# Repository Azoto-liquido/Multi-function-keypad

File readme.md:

# Multi-function keypad

This is a 4 switches keypad with a rotary encoder and an OLED display, it has 2 LEDs and uses QMK Firmware.

I made it to learn a bit of this topic and I think it is perfect for general porpouse, everyday shortcuts and macros in gaming. Also in the little display you could write your name or a motd.

## Bill of Materials
- 4x Cherry MX Switches
- 4x DSA Keycaps
- 4x M3x16mm SHCS Bolts
- 2x sk6812mini LEDs
- 1x 0.91" 128x32 OLED Display
- 1x EC11 Rotary Encoder
- 1x XIAO RP2040
- 1x Case (2 printed parts)

## Cad
The 2 parts are held together with 4 M3x16mm SHCS Bolts without heatset inserts (the threads are cut directly into the plastic). The case has a 4 degrees titl for better ergonomics.

Made in Fusion 360.

## PCB

Schematic:

PCB:

## Firmware Overview
The firmware uses QMK Firmware and is fully configurable with VIA.
- The rotary encoder serves as a volume controller.
- The 4 keys can be assigned to any key with VIAA (https://caniusevia.com/).
- Holding down the 4th key will activate another layer in which the keys can be assigned to any other function.
- The OLED display can be assigned to display any text (Always in VIA).
- The 2 LEDs can display any color (This is also done in VIA).

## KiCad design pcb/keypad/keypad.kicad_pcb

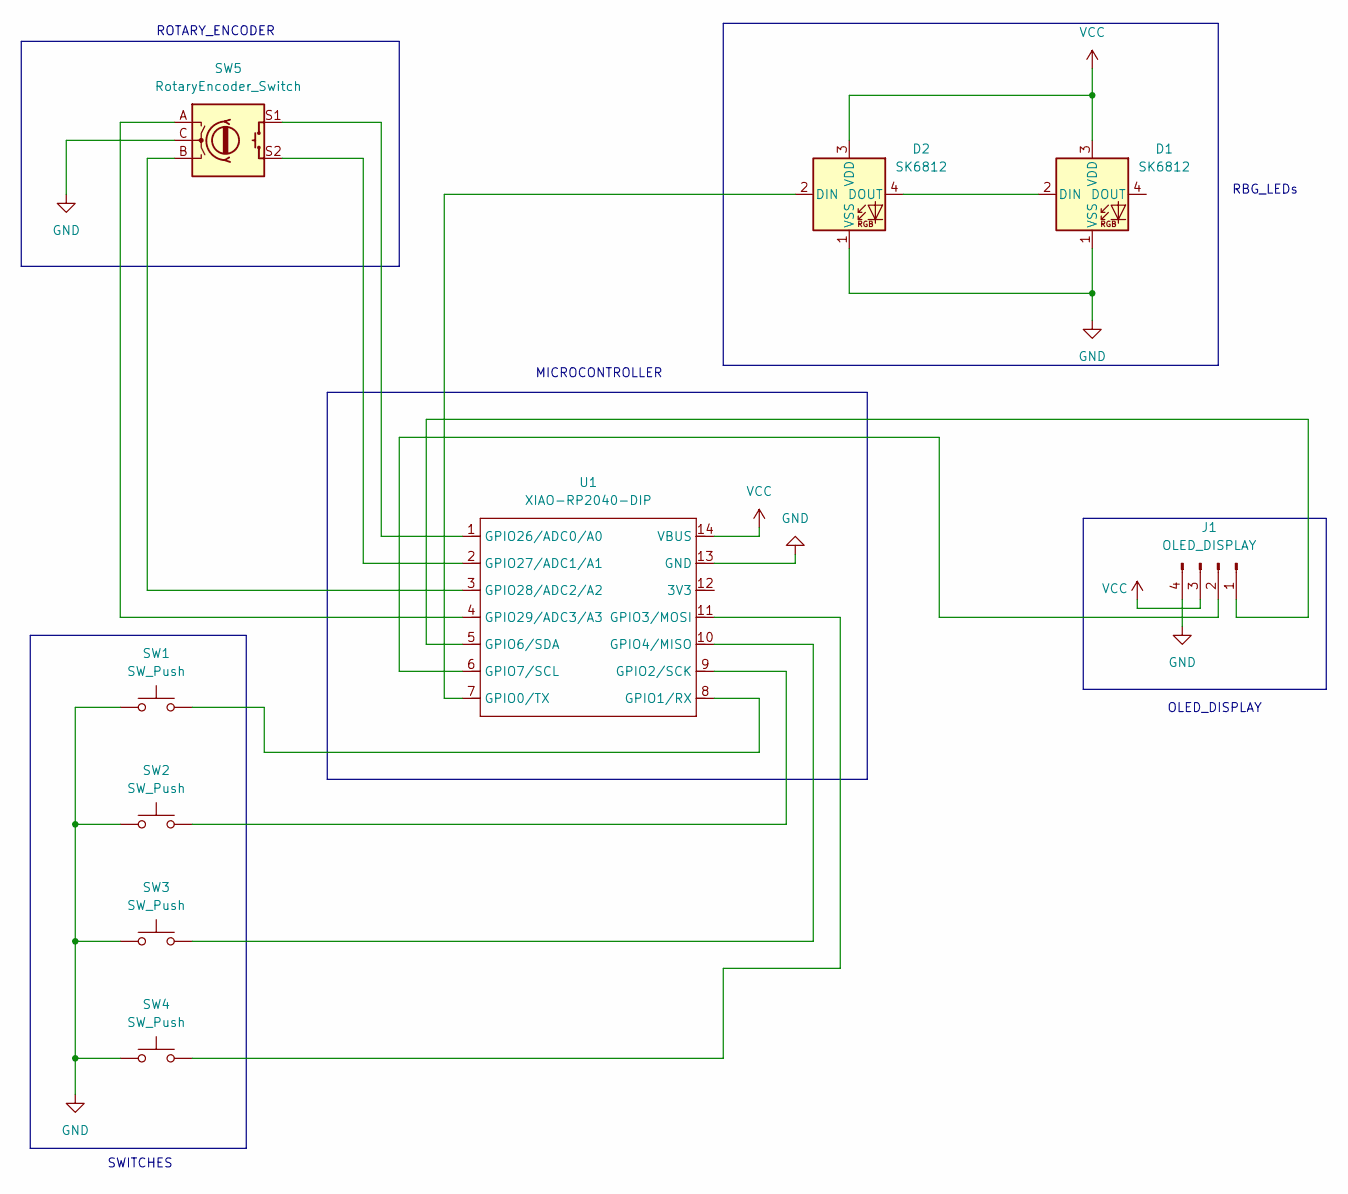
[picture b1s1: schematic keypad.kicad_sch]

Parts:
D1, D2: SK6812; LED_SK6812MINI_PLCC4_3.5x3.5mm_P1.75mm
J1: OLED_DISPLAY; PinHeader_1x04_P2.54mm_Vertical
SW1, SW2, SW3, SW4: SW_Push; SW_Cherry_MX_1.00u_PCB
SW5: RotaryEncoder_Switch; RotaryEncoder_Alps_EC11E-Switch_Vertical_H20mm
U1: XIAO-RP2040-DIP

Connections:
GND: D1.1 (VSS), D2.1 (VSS), J1.4, SW1.1, SW2.1, SW3.1, SW4.1, SW5.C, U1.13 (GND)
unnamed: D1.2 (DIN), D2.4 (DOUT)
unnamed: D2.2 (DIN), U1.7 (GPIO0/TX)
unnamed: J1.1, U1.5 (GPIO6/SDA)
unnamed: J1.2, U1.6 (GPIO7/SCL)
unnamed: SW1.2, U1.8 (GPIO1/RX)
unnamed: SW2.2, U1.9 (GPIO2/SCK)
unnamed: SW4.2, U1.11 (GPIO3/MOSI)
unnamed: SW3.2, U1.10 (GPIO4/MISO)
unnamed: SW5.S1, U1.1 (GPIO26/ADC0/A0)
unnamed: SW5.S2, U1.2 (GPIO27/ADC1/A1)
unnamed: SW5.B, U1.3 (GPIO28/ADC2/A2)
unnamed: SW5.A, U1.4 (GPIO29/ADC3/A3)
VCC: D1.3 (VDD), D2.3 (VDD), J1.3, U1.14 (VBUS)

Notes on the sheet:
OLED_DISPLAY
MICROCONTROLLER
RBG_LEDs
ROTARY_ENCODER
SWITCHES

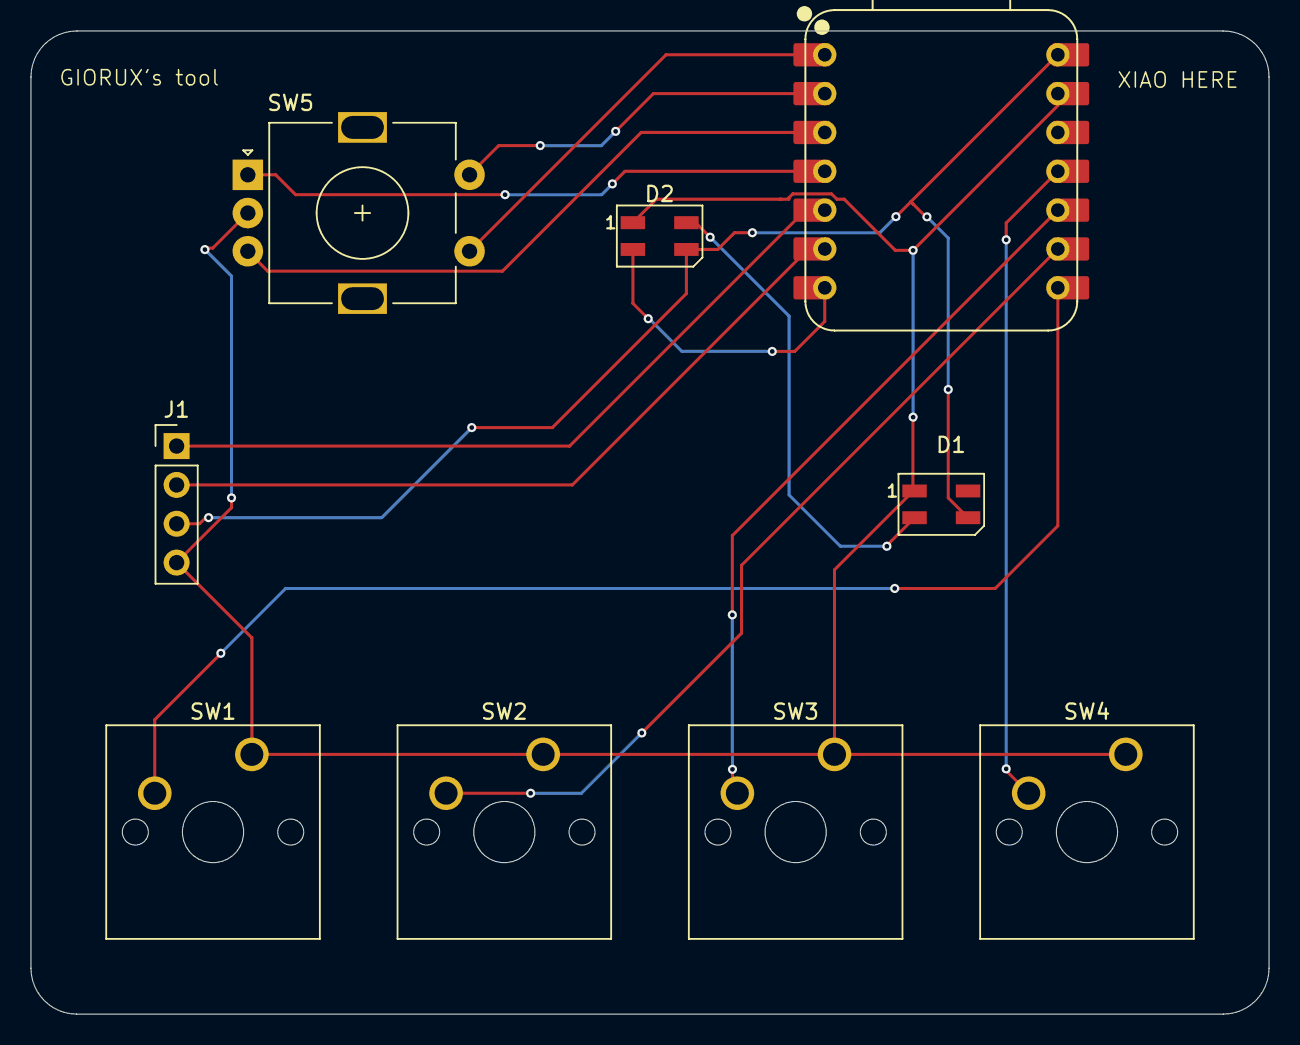
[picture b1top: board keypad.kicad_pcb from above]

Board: 2 copper layers, 81.0 x 64.3 mm, 9 parts (0 on the bottom side), 14 nets.

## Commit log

2026-03-22 Add 3D render
2026-03-22 Add 3d files and pcb files
2026-03-22 Fix error in pcb
2026-03-22 Add qmk software files
2026-03-27 Fixes in folder organization
2026-03-27 Major fixes in firmware and gerbers uploaded
